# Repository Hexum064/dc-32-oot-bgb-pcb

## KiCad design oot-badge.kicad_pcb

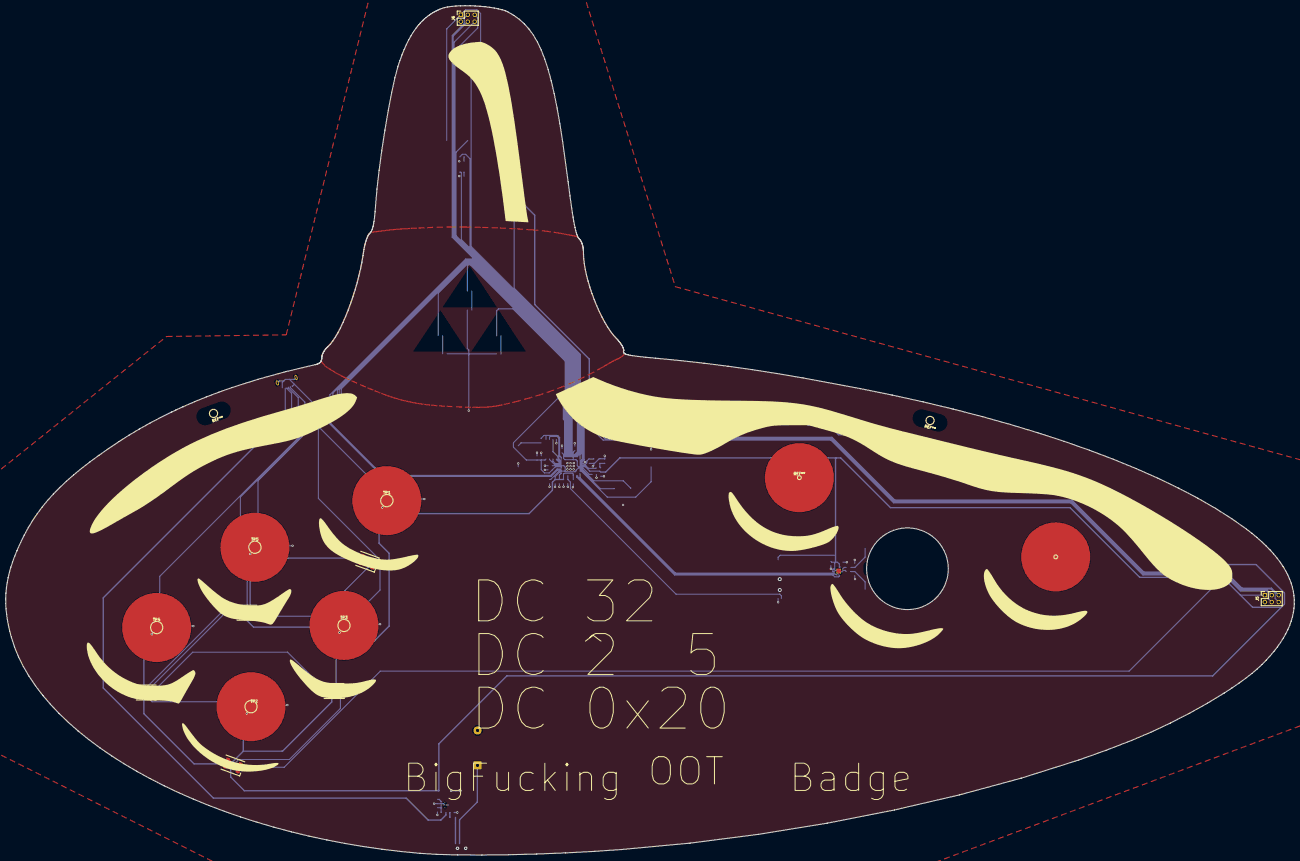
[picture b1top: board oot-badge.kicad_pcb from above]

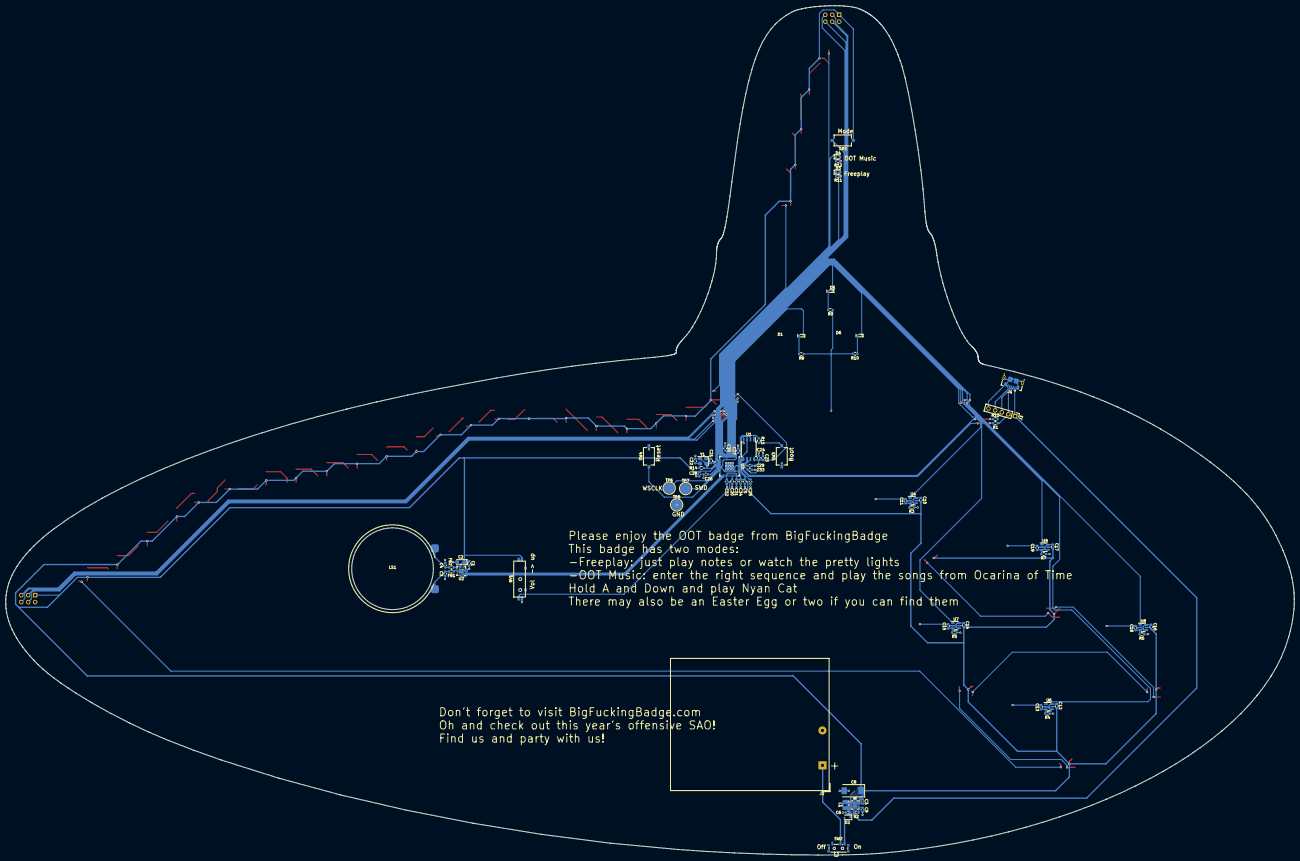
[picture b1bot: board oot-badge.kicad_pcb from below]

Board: 2 copper layers, 473.2 x 311.9 mm, 119 parts (80 on the bottom side), 97 nets.

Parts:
C1, C9, C10, C12, C14, C16, C17, C23: 0.1uF; C_0603_1608Metric
C2: 10uF; CP_EIA-3216-18_Kemet-A
C3, C4: 220pF; C_0603_1608Metric
C5, C20, C24, C25, C34: 2.2uF; C_0603_1608Metric
C6, C7: 10uF; C_0603_1608Metric
C8: 470uF; CP_EIA-7343-31_Kemet-D
C11, C13, C15, C18, C19: 47pF; C_0603_1608Metric
C21, C22: 15pf; C_0603_1608Metric
C26, C27, C28, C29, C30, C31, C32, C33: .1uF; C_0603_1608Metric
D1, D5, D6: LED; TJ-S1706CL6T5ALC9Y-A5
D2: diode; D_SOD-323
D3, D4: Blue LED; LED_0603_1608Metric
D7, D8, D9, D10, D11, D12, D13, D14, D15, D16, D17, D18, D19, D20, D21, D22, D23, D24, D25, D26, D27, D28, D29, D30, D31, D32, D33, D34, D35, D36, D37, D38: WS2812B; LED_WS2812B_PLCC4_5.0x5.0mm_P3.2mm
FB1, FB2: 120 Ohms @ 100 MHz; R_0603_1608Metric
J2: Power; BatteryHolder_TruPower_BH-331P_3xAA
J3: Conn_01x04; PinHeader_1x05_P2.54mm_Vertical
J4: USB_B_Micro; USB_Micro-B_GCT_USB3076-30-A
J5, J6: Conn_02x03_Odd_Even; PinSocket_2x03_P2.54mm_Vertical
L1: 2.2uH; L_1008_2520Metric
LS1: Speaker; FS32MS0410-H5.1
R1, R13: 27; R_0603_1608Metric
R2: 100; R_0603_1608Metric
R3, R4, R5, R6, R7: 4.7k; R_0603_1608Metric
R8, R9, R10, R11, R12: 470; R_0603_1608Metric
R14, R15: 1k; R_0603_1608Metric
RV1: 10K; RS08U111Z001
SW1: mode; SW_Tactile_SPST_NO_Straight_CK_PTS636Sx25SMTRLFS
SW2: power; SW_SPDT_PCM12
SW3: boot; SW_Tactile_SPST_NO_Straight_CK_PTS636Sx25SMTRLFS
SW4: rst; SW_Tactile_SPST_NO_Straight_CK_PTS636Sx25SMTRLFS
TP1: TouchPad D; TestPoint_Pad_D4.0mm
TP2: TouchPad F; TestPoint_Pad_D4.0mm
TP3: TouchPad A; TestPoint_Pad_D4.0mm
TP4: TouchPad B; TestPoint_Pad_D4.0mm
TP5: TouchPad D2; TestPoint_Pad_D4.0mm
TP6: swclk; TestPoint_Pad_D4.0mm
TP7, TP8: swd; TestPoint_Pad_D4.0mm
U1: W25Q32JVSS; SOIC-8_5.23x5.23mm_P1.27mm
U2: MAX98357AETE+; QFN-16-1EP_3x3mm_P0.5mm_EP1.75x1.75mm_ThermalVias
U3: RP2040; QFN-56-1EP_7x7mm_P0.4mm_EP3.2x3.2mm
U4, U6, U7, U8, U9: SOT-23-6
U5: TPS63001DRCR; VREG_V62_16624-01YE
Y1: 12Mhz; Crystal_SMD_3225-4Pin_3.2x2.5mm

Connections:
+1V1: C25.1, C26.1, C29.1, U3.23 (DVDD), U3.45 (VREG_VOUT), U3.50 (DVDD)
+3.3V: C1.1, C2.1, C5.1, C7.1, C8.1, C10.1, C12.1, C14.1, C16.1, C17.1, C23.1, C24.1, C27.1, C28.1, C30.1, C31.1, C32.1, C33.1, C34.1, D7.1 (VDD), D8.1 (VDD), D9.1 (VDD), D10.1 (VDD), D11.1 (VDD), D12.1 (VDD), D13.1 (VDD), D14.1 (VDD), D15.1 (VDD), D16.1 (VDD), D17.1 (VDD), D18.1 (VDD), D19.1 (VDD), D20.1 (VDD), D21.1 (VDD), D22.1 (VDD), D23.1 (VDD), D24.1 (VDD), D25.1 (VDD), D26.1 (VDD), D27.1 (VDD), D28.1 (VDD), D29.1 (VDD), D30.1 (VDD), D31.1 (VDD), D32.1 (VDD), D33.1 (VDD), D34.1 (VDD), D35.1 (VDD), D36.1 (VDD), D37.1 (VDD), D38.1 (VDD), J5.1, J6.1, RV1.3, SW1.1, U1.8 (VCC), U2.2 (GAIN_SLOT), U2.4 (*SD_MODE), U2.7 (VDD), U2.8 (VDD), U3.1 (IOVDD), U3.10 (IOVDD), U3.22 (IOVDD), U3.33 (IOVDD), U3.42 (IOVDD), U3.43 (ADC_AVDD), U3.44 (VREG_IN), U3.48 (USB_VDD), U3.49 (IOVDD), U4.5 (Vcc), U5.1 (VOUT), U5.10 (FB), U6.5 (Vcc), U7.5 (Vcc), U8.5 (Vcc), U9.5 (Vcc)
+BATT: J2.1, SW2.2 (B)
GND: C1.2, C2.2, C3.1, C4.2, C5.2, C6.2, C7.2, C8.2, C9.2, C10.2, C11.2, C12.2, C13.2, C14.2, C15.2, C16.2, C17.2, C18.2, C19.2, C20.2, C21.2, C22.2, C23.2, C24.2, C25.2, C26.2, C27.2, C28.2, C29.2, C30.2, C31.2, C32.2, C33.2, C34.2, D7.3 (VSS), D8.3 (VSS), D9.3 (VSS), D10.3 (VSS), D11.3 (VSS), D12.3 (VSS), D13.3 (VSS), D14.3 (VSS), D15.3 (VSS), D16.3 (VSS), D17.3 (VSS), D18.3 (VSS), D19.3 (VSS), D20.3 (VSS), D21.3 (VSS), D22.3 (VSS), D23.3 (VSS), D24.3 (VSS), D25.3 (VSS), D26.3 (VSS), D27.3 (VSS), D28.3 (VSS), D29.3 (VSS), D30.3 (VSS), D31.3 (VSS), D32.3 (VSS), D33.3 (VSS), D34.3 (VSS), D35.3 (VSS), D36.3 (VSS), D37.3 (VSS), D38.3 (VSS), J2.2, J3.5, J4.5 (GND), J4.6 (Shield), J5.2, J6.2, R8.1, R9.1, R10.1, R11.1, R12.1, RV1.1, SW3.1, SW4.2, TP8.1, U1.4 (GND), U2.3 (GND), U2.11 (GND), U2.15 (GND), U2.17 (EPAD), U3.19 (TESTEN), U3.57 (GND), U4.2 (Gnd), U4.4 (AHL), U4.6 (Tog), U5.3 (PGND), U5.9 (GND), U5.11 (THERMAL_PAD), U6.2 (Gnd), U6.4 (AHL), U6.6 (Tog), U7.2 (Gnd), U7.4 (AHL), U7.6 (Tog), U8.2 (Gnd), U8.4 (AHL), U8.6 (Tog), U9.2 (Gnd), U9.4 (AHL), U9.6 (Tog), Y1.2, Y1.4
unnamed: C3.2, FB1.1, LS1.2
unnamed: C4.1, FB2.1, LS1.1
unnamed: C22.1, R14.1, Y1.3
unnamed: D1.2 (A), U3.4 (GPIO2)
unnamed: D1.1 (K), R8.2
unnamed: D2.2 (A), SW2.3 (C)
unnamed: C6.1, D2.1 (K), J3.1, J4.1 (VBUS), R2.1, U5.5 (VIN)
unnamed: D3.2 (A), U3.14 (GPIO11)
unnamed: D3.1 (K), R11.2
unnamed: D4.2 (A), U3.15 (GPIO12)
unnamed: D4.1 (K), R12.2
unnamed: D5.2 (A), U3.5 (GPIO3)
unnamed: D5.1 (K), R9.2
unnamed: D6.2 (A), U3.6 (GPIO4)
unnamed: D6.1 (K), R10.2
unnamed: D7.4 (DIN), U3.16 (GPIO13)
unnamed: D7.2 (DOUT), D8.4 (DIN)
unnamed: D8.2 (DOUT), D9.4 (DIN)
unnamed: D9.2 (DOUT), D10.4 (DIN)
unnamed: D10.2 (DOUT), D11.4 (DIN)
unnamed: D11.2 (DOUT), D12.4 (DIN)
unnamed: D12.2 (DOUT), D13.4 (DIN)
unnamed: D13.2 (DOUT), D14.4 (DIN)
unnamed: D14.2 (DOUT), D15.4 (DIN)
unnamed: D15.2 (DOUT), D16.4 (DIN)
unnamed: D16.2 (DOUT), D17.4 (DIN)
unnamed: D17.2 (DOUT), D18.4 (DIN)
unnamed: D18.2 (DOUT), D19.4 (DIN)
unnamed: D19.2 (DOUT), D20.4 (DIN)
unnamed: D20.2 (DOUT), D21.4 (DIN)
unnamed: D21.2 (DOUT), D22.4 (DIN)
unnamed: D22.2 (DOUT), D23.4 (DIN)
unnamed: D23.2 (DOUT), D24.4 (DIN)
unnamed: D24.2 (DOUT), D25.4 (DIN)
unnamed: D25.2 (DOUT), D26.4 (DIN)
unnamed: D26.2 (DOUT), D27.4 (DIN)
unnamed: D27.2 (DOUT), D28.4 (DIN)
unnamed: D28.2 (DOUT), D29.4 (DIN)
unnamed: D29.2 (DOUT), D30.4 (DIN)
unnamed: D30.2 (DOUT), D31.4 (DIN)
unnamed: D31.2 (DOUT), D32.4 (DIN)
unnamed: D32.2 (DOUT), D33.4 (DIN)
unnamed: D33.2 (DOUT), D34.4 (DIN)
unnamed: D34.2 (DOUT), D35.4 (DIN)
unnamed: D35.2 (DOUT), D36.4 (DIN)
unnamed: D36.2 (DOUT), D37.4 (DIN)
unnamed: D37.2 (DOUT), D38.4 (DIN)
unnamed: J3.2, J4.2 (D-), R1.1
unnamed: J3.3, J4.3 (D+), R13.2
unnamed: J3.4, J4.4 (ID)
unnamed: J5.3, J6.3, U3.2 (GPIO0)
unnamed: J5.4, J6.4, U3.3 (GPIO1)
unnamed: J5.5, J6.5, U3.17 (GPIO14)
unnamed: J5.6, J6.6, U3.18 (GPIO15)
unnamed: R3.1, TP1.1
unnamed: R4.1, TP2.1
unnamed: R5.1, TP3.1
unnamed: R6.1, TP4.1
unnamed: R7.1, TP5.1
unnamed: R15.1, SW3.2
unnamed: U1.6 (CLK), U3.52 (QSPI_SCLK)
unnamed: U1.5 (DI(IO0)), U3.53 (QSPI_SD0)
unnamed: U1.2 (DO(IO1)), U3.55 (QSPI_SD1)
unnamed: U1.3 (IO2), U3.54 (QSPI_SD2)
unnamed: U1.7 (IO3), U3.51 (QSPI_SD3)
unnamed: R15.2, U1.1 (~CS), U3.56 (QSPI_SS)
unnamed: U2.16 (BCLK), U3.29 (GPIO18)
unnamed: U2.1 (DIN), U3.28 (GPIO17)
unnamed: U2.14 (LRCLK), U3.30 (GPIO19)
unnamed: FB1.2, U2.10 (OUTN)
unnamed: FB2.2, U2.9 (OUTP)
unnamed: U3.7 (GPIO5), U4.1 (Out)
unnamed: U3.8 (GPIO6), U6.1 (Out)
unnamed: U3.9 (GPIO7), U7.1 (Out)
unnamed: U3.11 (GPIO8), U8.1 (Out)
unnamed: U3.12 (GPIO9), U9.1 (Out)
unnamed: SW1.2, U3.13 (GPIO10)
unnamed: C20.1, RV1.2, U3.38 (GPIO26_ADC0)
unnamed: SW4.1, U3.26 (RUN)
unnamed: TP6.1, U3.24 (SWCLK)
unnamed: TP7.1, U3.25 (SWD)
unnamed: R1.2, U3.46 (USB_DM)
unnamed: R13.1, U3.47 (USB_DP)
unnamed: C21.1, U3.20 (XIN), Y1.1
unnamed: R14.2, U3.21 (XOUT)
unnamed: C11.1, R3.2, U4.3 (Key)
unnamed: C9.1, R2.2, U5.6 (EN), U5.7 (PS/SYNC), U5.8 (VINA)
unnamed: L1.2, U5.4 (L1)
unnamed: L1.1, U5.2 (L2)
unnamed: C13.1, R4.2, U6.3 (Key)
unnamed: C15.1, R5.2, U7.3 (Key)
unnamed: C18.1, R6.2, U8.3 (Key)
unnamed: C19.1, R7.2, U9.3 (Key)

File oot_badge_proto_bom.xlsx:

Qty | Designator | Comment | Footprint | Part # | src
8 | C1, C9, C10, C12, C14, C16, C17, C23 | 0.1uF | Capacitor_SMD:C_0603_1608Metric | C14663 | jlc
1 | C2 | 10uF | Capacitor_Tantalum_SMD:CP_EIA-3216-18_Kemet-A | C177743 | jlc
2 | C3, C4 | 220pF | Capacitor_SMD:C_0603_1608Metric | C1603 | jlc
5 | C5, C20, C24, C25, C34 | 2.2uF | Capacitor_SMD:C_0603_1608Metric | C23630 | jlc
2 | C6, C7 | 10uF | Capacitor_SMD:C_0603_1608Metric | C19702 | jlc
1 | C8 | 470uF | Capacitor_Tantalum_SMD:CP_EIA-7343-31_Kemet-D | TCMOJ477DTLSR100 | digikey
5 | C11, C13, C15, C18, C19 | 47pF | Capacitor_SMD:C_0603_1608Metric | C1671 | jlc
2 | C21, C22 | 15pf | Capacitor_SMD:C_0603_1608Metric | C1644 | jlc
8 | C26, C27, C28, C29, C30, C31, C32, C33 | .1uF | Capacitor_SMD:C_0603_1608Metric | C15849 | jlc
3 | D1, D5, D6 | LED | LED_SMD:TJ-S1706CL6T5ALC9Y-A5 | C1322337 | jlc
1 | D2 | diode | Diode_SMD:D_SOD-323 | C191023 | jlc
2 | D3, D7 | Blue LED | LED_SMD:LED_0603_1608Metric | C7496819 | lcsc
32 | D4, D8, D9, D10, D11, D12, D13, D14, D15, D16, D17, D18, D19, D20, D21, D22, D2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 | WS2812B | LED_SMD:LED_WS2812B_PLCC4_5.0x5.0mm_P3.2mm | C2843785 | jlc
2 | FB1, FB2 | 120 Ohms @ 100 MHz | Resistor_SMD:R_0603_1608Metric | C275439 | jlc
1 | J1 | Conn_02x02_Odd_Even | Connector_PinHeader_2.54mm:PinHeader_2x02_P2.54mm_Vertical
1 | J2 | Power | Connector_PinHeader_2.54mm:PinHeader_1x02_P2.54mm_Vertical
1 | J3 | Conn_01x04 | Connector_PinHeader_2.54mm:PinHeader_1x05_P2.54mm_Vertical
1 | J4 | USB_B_Micro | Connector_USB:USB_Micro-B_GCT_USB3076-30-A
2 | J5, J6 | Conn_02x03_Odd_Even | Connector_PinSocket_2.54mm:PinSocket_2x03_P2.54mm_Vertical | S9717-ND | digikey
3 | JP1, JP2, JP3 | Jumper_2_Bridged | Connector_PinHeader_2.54mm:PinHeader_1x02_P2.54mm_Vertical
1 | L1 | 2.2uH | Inductor_SMD:L_1008_2520Metric | C315713 | jlc
1 | LS1 | Speaker | Buzzer_Beeper:FS32MS0410-H5.1 | C482332 | jlc
2 | R1, R13 | 27 | Resistor_SMD:R_0603_1608Metric | C25190 | jlc
1 | R2 | 100 | Resistor_SMD:R_0603_1608Metric | C22775 | jlc
5 | R3, R4, R5, R6, R7 | 4.7k | Resistor_SMD:R_0603_1608Metric | C23162 | jlc
5 | R8, R9, R10, R11, R12 | 470 | Resistor_SMD:R_0603_1608Metric | C23179 | jlc
2 | R14, R15 | 1k | Resistor_SMD:R_0603_1608Metric | C21190 | jlc
1 | RV1 | 10K | Potentiometer_SMD:RS08U111Z001 | C202411 | jlc
1 | SW1 | mode | Button_Switch_SMD:SW_Tactile_SPST_NO_Straight_CK_PTS636Sx25SMTRLFS | C318938 | jlc
1 | SW2 | power | Button_Switch_SMD:SW_SPDT_PCM12 | C2681568 | jlc
1 | SW3 | boot | Button_Switch_SMD:SW_Tactile_SPST_NO_Straight_CK_PTS636Sx25SMTRLFS | C318938 | jlc
1 | SW4 | rst | Button_Switch_SMD:SW_Tactile_SPST_NO_Straight_CK_PTS636Sx25SMTRLFS | C318938 | jlc
1 | U1 | W25Q32JVSS | Package_SO:SOIC-8_5.23x5.23mm_P1.27mm | C2940197 | jlc
1 | U2 | MAX98357AETE+ | Package_DFN_QFN:QFN-16-1EP_3x3mm_P0.5mm_EP1.75x1.75mm_ThermalVias | C910544 | jlc
1 | U3 | RP2040 | Package_DFN_QFN:QFN-56-1EP_7x7mm_P0.4mm_EP3.2x3.2mm | C2040 | jlc
5 | U4, U6, U7, U8, U9 | ~ | Package_TO_SOT_SMD:SOT-23-6 | C723856 | jlc
1 | U5 | TPS63001DRCR | TPS63001DRCR:VREG_V62_16624-01YE | C28060 | jlc
1 | Y1 | 12Mhz | Crystal:Crystal_SMD_3225-4Pin_3.2x2.5mm | C390763 | lcsc
